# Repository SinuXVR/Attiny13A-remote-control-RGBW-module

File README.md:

# Attiny13A based remote control RGB module

# Features

* 3 independent software PWM channel to control RGB led
* Works with cheap 24-key IR remote controller (NEC protocol)
* 16 static colors and 4 special effects
* 5 brightness levels (for static colors) and variable special effects speed
* Power ON/OFF feature
* Power consumption in OFF mode is less than 0.8mA (depends on IR receiver)
* Supply voltage: 3V to 6V (single Li-ion, 3xLR06, USB)
* Size: 868 bytes

# Remote controller

||
|:---:|
||

### Showcase

|||||
|:---:|:---:|:---:|:---:|

#### Special effects

|**Flash**|**Smooth**|
|:-------:|:--------:|
|||
|**Strobe**|**Fade**|
|||

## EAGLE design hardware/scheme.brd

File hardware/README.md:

# Circuit and board

|||
|:---:|:---:|

Made in EAGLE 9.4.2

# Bill Of Materials

|**Item**|**Quantity**|**Description**|
|:------:|:----------:|:--------------|
|D*|10|5050 RGB LED|
|Q*|3|SOT-23 N-channel MOSFET with Imax > 100mA (AO3400, IRLML2502TR)|
|R1, R3|2|15 Ohms 1206 resistor|
|R2|1|27 Ohms 1206 resistor|
|R4|1|100 Ohms 0805 resistor|
|C1|1|10pF 0805 capacitor|
|C2|1|10uF 1206 capacitor|
|U2|1|IR receiver (VS1838B, TSOP4838 or similar)|
|IC1|1|ATTINY13-20SSU|

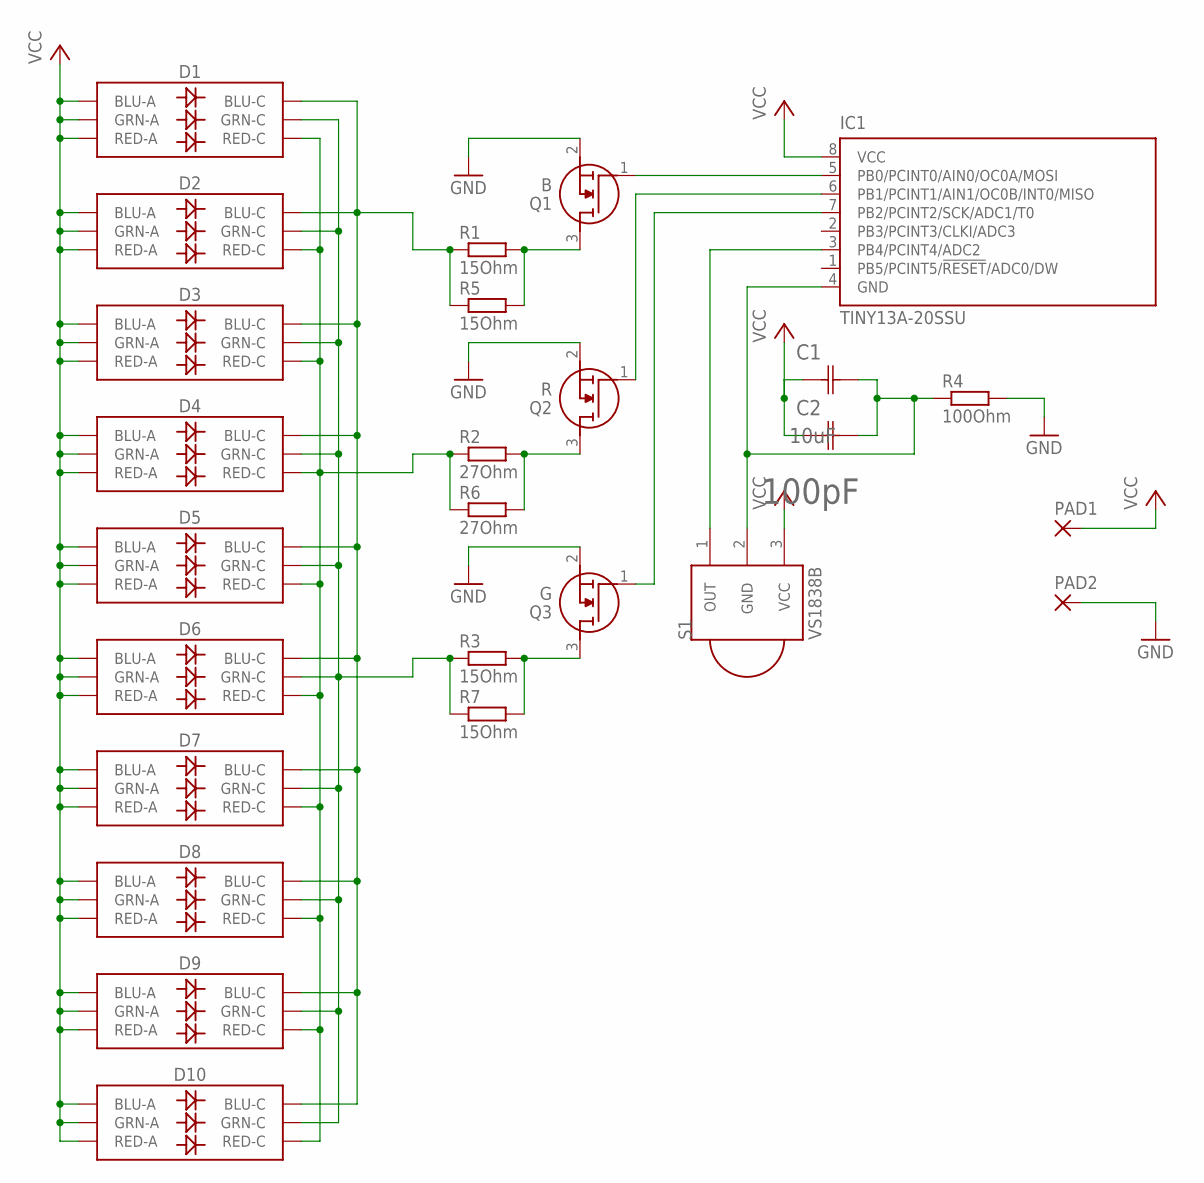
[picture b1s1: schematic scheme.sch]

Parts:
C1: 10uF; CAPC3216X94N
C2: 100pF; CAPC2013X94N
D1, D2, D3, D4, D5, D6, D7, D8, D9, D10: LED-RGBNO_IC; LED-TRICOLOR-5050
IC1: TINY13A-20SSU; 8S1
PAD1, PAD2: SMD2; SMD1,27-2,54
Q1: B; SOT95P280X125-3N
Q2: R; SOT95P280X125-3N
Q3: G; SOT95P280X125-3N
R1, R3: 15Ohm; R1206
R2: 27Ohm; R1206
R4: 100Ohm; R0805
R5, R7: 15Ohm; R0805
R6: 27Ohm; R0805
S1: VS1838B; PNA460XM

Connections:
GND: PAD2.1, Q1.2 (S), Q2.2 (S), Q3.2 (S), R4.2
unnamed: IC1.3 (PB4/PCINT4/ADC2), S1.1 (OUT)
unnamed: IC1.5 (PB0/PCINT0/AIN0/OC0A/MOSI), Q1.1 (G)
unnamed: IC1.6 (PB1/PCINT1/AIN1/OC0B/INT0/MISO), Q2.1 (G)
unnamed: IC1.7 (PB2/PCINT2/SCK/ADC1/T0), Q3.1 (G)
unnamed: D1.4 (GRN-C), D2.4 (GRN-C), D3.4 (GRN-C), D4.4 (GRN-C), D5.4 (GRN-C), D6.4 (GRN-C), D7.4 (GRN-C), D8.4 (GRN-C), D9.4 (GRN-C), D10.4 (GRN-C), R3.1, R7.1
unnamed: D1.6 (BLU-C), D2.6 (BLU-C), D3.6 (BLU-C), D4.6 (BLU-C), D5.6 (BLU-C), D6.6 (BLU-C), D7.6 (BLU-C), D8.6 (BLU-C), D9.6 (BLU-C), D10.6 (BLU-C), R1.1, R5.1
unnamed: Q1.3 (D), R1.2, R5.2
unnamed: Q2.3 (D), R2.2, R6.2
unnamed: Q3.3 (D), R3.2, R7.2
unnamed: C1.2 (C2), C2.2 (C2), IC1.4 (GND), R4.1, S1.2 (GND)
unnamed: D1.5 (RED-C), D2.5 (RED-C), D3.5 (RED-C), D4.5 (RED-C), D5.5 (RED-C), D6.5 (RED-C), D7.5 (RED-C), D8.5 (RED-C), D9.5 (RED-C), D10.5 (RED-C), R2.1, R6.1
VCC: C1.1 (C1), C2.1 (C1), D1.1 (BLU-A), D1.2 (RED-A), D1.3 (GRN-A), D2.1 (BLU-A), D2.2 (RED-A), D2.3 (GRN-A), D3.1 (BLU-A), D3.2 (RED-A), D3.3 (GRN-A), D4.1 (BLU-A), D4.2 (RED-A), D4.3 (GRN-A), D5.1 (BLU-A), D5.2 (RED-A), D5.3 (GRN-A), D6.1 (BLU-A), D6.2 (RED-A), D6.3 (GRN-A), D7.1 (BLU-A), D7.2 (RED-A), D7.3 (GRN-A), D8.1 (BLU-A), D8.2 (RED-A), D8.3 (GRN-A), D9.1 (BLU-A), D9.2 (RED-A), D9.3 (GRN-A), D10.1 (BLU-A), D10.2 (RED-A), D10.3 (GRN-A), IC1.8 (VCC), PAD1.1, S1.3 (VCC)

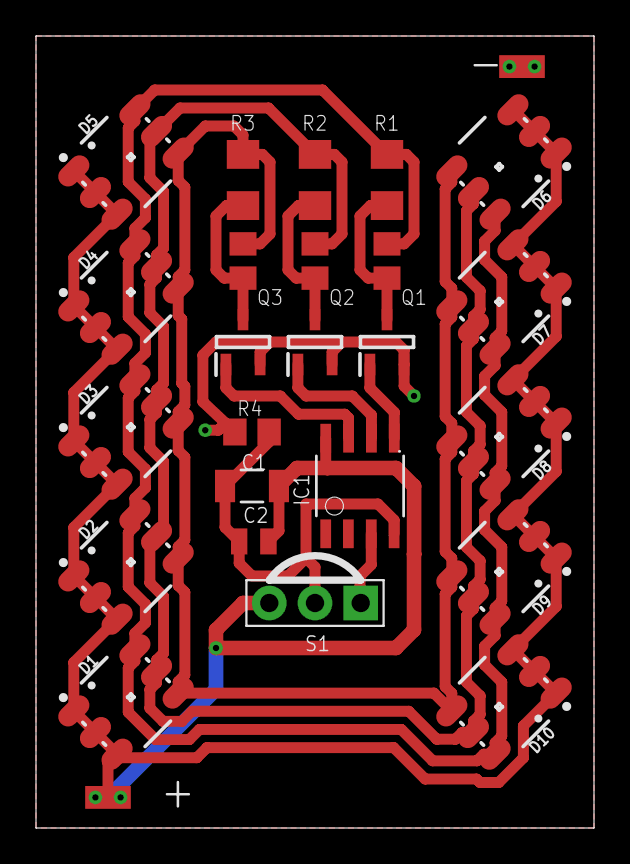
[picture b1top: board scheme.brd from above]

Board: 2 copper layers, 31.0 x 44.0 mm, 26 parts (0 on the bottom side), 13 nets.

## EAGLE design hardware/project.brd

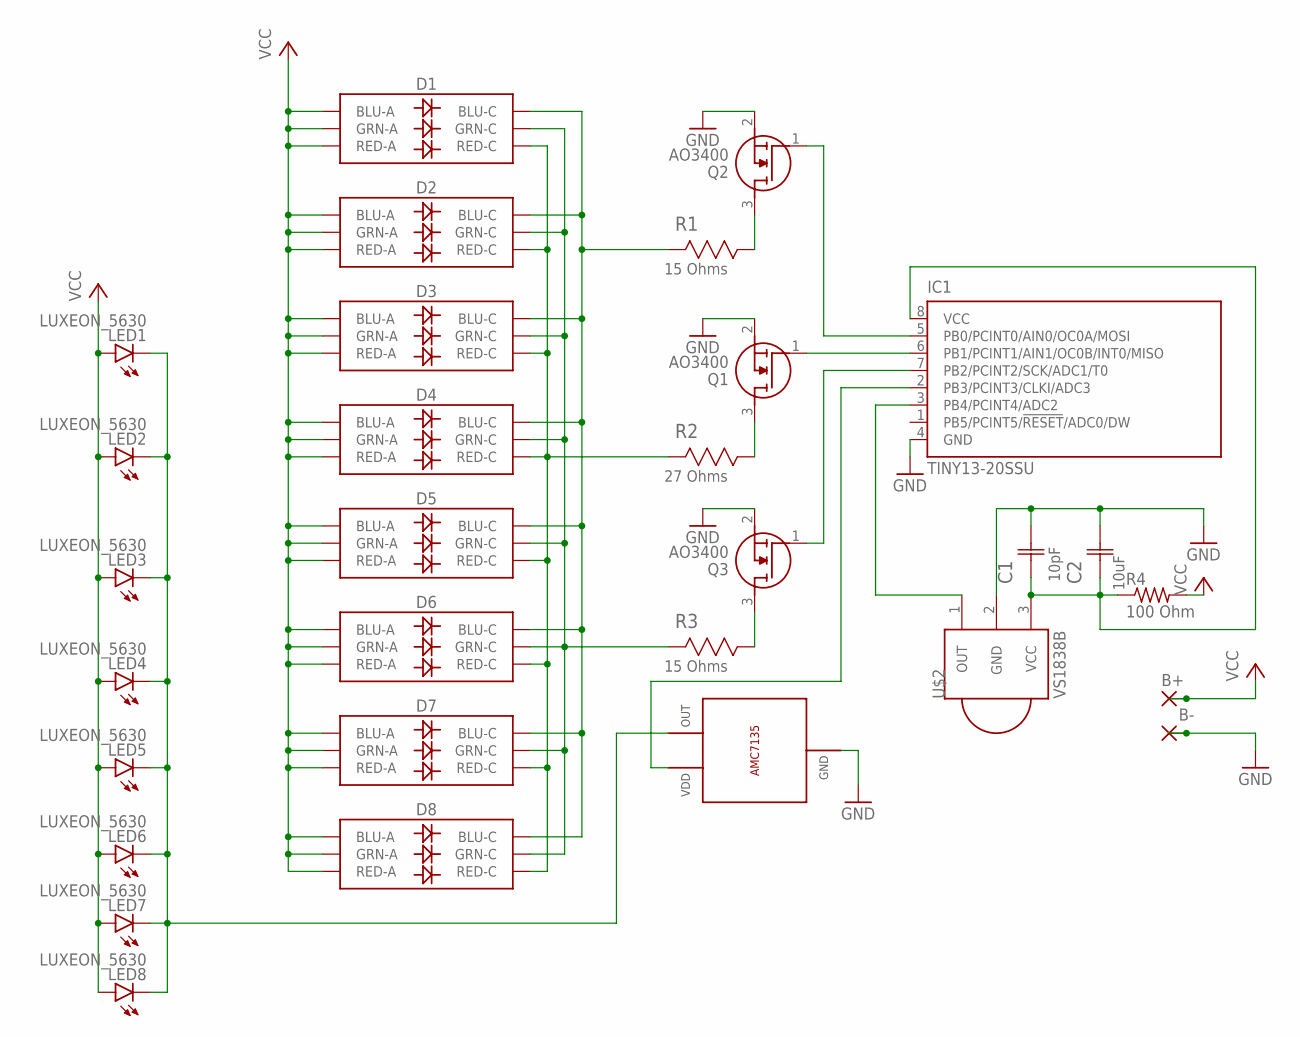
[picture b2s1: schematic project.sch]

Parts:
B+: WIREPADSMD1,27-254; SMD1,27-2,54
B-: WIREPADSMD1,27-254; SMD1,27-2,54
C1: 10pF; CAPC2013X94N
C2: 10uF; CAPC3216X94N
D1, D2, D3, D4, D5, D6, D7, D8: LED-RGBNO_IC; LED-TRICOLOR-5050
IC1: TINY13-20SSU; 8S1
LED1, LED2, LED3, LED4, LED5, LED6, LED7, LED8: LUXEON_5630
Q1, Q2, Q3: AO3400; SOT95P280X125-3N
R1, R3: 15 Ohms; RESC3216X71N
R2: 27 Ohms; RESC3216X71N
R4: 100 Ohm; R0805
U$1: AMC7135
U$2: VS1838B; PNA460XM

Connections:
GND: B-.1, C1.2 (C2), C2.2 (C2), IC1.4 (GND), Q1.2 (S), Q2.2 (S), Q3.2 (S), U$1.GND, U$1.TAB (GND), U$2.2 (GND)
unnamed: LED1.1@1 (C), LED1.1@2 (C), LED2.1@1 (C), LED2.1@2 (C), LED3.1@1 (C), LED3.1@2 (C), LED4.1@1 (C), LED4.1@2 (C), LED5.1@1 (C), LED5.1@2 (C), LED6.1@1 (C), LED6.1@2 (C), LED7.1@1 (C), LED7.1@2 (C), LED8.1@1 (C), LED8.1@2 (C), U$1.OUT
unnamed: IC1.5 (PB0/PCINT0/AIN0/OC0A/MOSI), Q2.1 (G)
unnamed: IC1.6 (PB1/PCINT1/AIN1/OC0B/INT0/MISO), Q1.1 (G)
unnamed: IC1.7 (PB2/PCINT2/SCK/ADC1/T0), Q3.1 (G)
unnamed: Q2.3 (D), R1.1 (R1)
unnamed: Q1.3 (D), R2.1 (R1)
unnamed: Q3.3 (D), R3.1 (R1)
unnamed: D1.5 (RED-C), D2.5 (RED-C), D3.5 (RED-C), D4.5 (RED-C), D5.5 (RED-C), D6.5 (RED-C), D7.5 (RED-C), D8.5 (RED-C), R2.2 (R2)
unnamed: D1.6 (GRN-C), D2.6 (GRN-C), D3.6 (GRN-C), D4.6 (GRN-C), D5.6 (GRN-C), D6.6 (GRN-C), D7.6 (GRN-C), D8.6 (GRN-C), R3.2 (R2)
unnamed: D1.4 (BLU-C), D2.4 (BLU-C), D3.4 (BLU-C), D4.4 (BLU-C), D5.4 (BLU-C), D6.4 (BLU-C), D7.4 (BLU-C), D8.4 (BLU-C), R1.2 (R2)
unnamed: IC1.3 (PB4/PCINT4/ADC2), U$2.1 (OUT)
unnamed: IC1.2 (PB3/PCINT3/CLKI/ADC3), U$1.VDD
unnamed: C1.1 (C1), C2.1 (C1), IC1.8 (VCC), R4.1, U$2.3 (VCC)
VCC: B+.1, D1.1 (GRN-A), D1.2 (RED-A), D1.3 (BLU-A), D2.1 (GRN-A), D2.2 (RED-A), D2.3 (BLU-A), D3.1 (GRN-A), D3.2 (RED-A), D3.3 (BLU-A), D4.1 (GRN-A), D4.2 (RED-A), D4.3 (BLU-A), D5.1 (GRN-A), D5.2 (RED-A), D5.3 (BLU-A), D6.1 (GRN-A), D6.2 (RED-A), D6.3 (BLU-A), D7.1 (GRN-A), D7.2 (RED-A), D7.3 (BLU-A), D8.1 (GRN-A), D8.2 (RED-A), D8.3 (BLU-A), LED1.2 (A), LED2.2 (A), LED3.2 (A), LED4.2 (A), LED5.2 (A), LED6.2 (A), LED7.2 (A), LED8.2 (A), R4.2

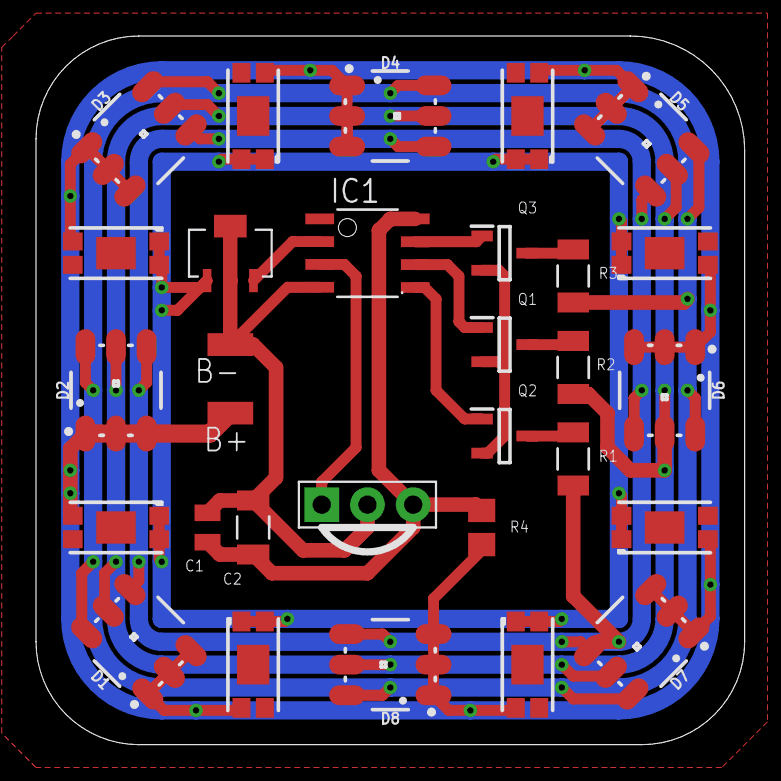
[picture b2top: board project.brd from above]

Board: 2 copper layers, 39.4 x 39.4 mm, 30 parts (0 on the bottom side), 15 nets.

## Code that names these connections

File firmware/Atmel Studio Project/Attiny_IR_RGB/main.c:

/**
 * Chip type: Attiny13
 * Clock frequency: 4.8MHz without divider
 * Flash command: avrdude -p t13 -c avrisp -b 19200 -u -Uflash:w:Attiny_IR_RGB.hex:a -Ulfuse:w:0x71:m -Uhfuse:w:0xFF:m
 *                       +--------+
 *        [        (PB5) |1*     8| (VCC)  Power ]
 *        [        (PB3) |2      7| (PB2)   BLUE ]
 *        [ VS1838 (PB4) |3      6| (PB1)  GREEN ]
 *        [ Ground (GND) |4      5| (PB0)    RED ]
 *                       +--------+
 */

#define F_CPU 4800000UL
#include <avr/io.h>
#include "lib/common.h"
#include "lib/ir.h"
#include "lib/led_pwm.h"
#include "lib/animation.h"

// Entry point
int main(void) {
	// Set up
	power_off_init();
	pwm_init_rgb();
	ir_init();
	
	// Initial state - STATE_COLOR with power off bit
	byte current_state = STATE_COLOR | 0x80;
	
	// Animation and brightness parameters
	byte anim_rate = ANIM_RATE_INITIAL_VALUE;
	byte anim_counter = 0;
	byte anim_local_counter = 0;
	byte brightness = BRIGHTNESS_INITIAL_VALUE;
	
	// Main loop
	while(1) {
		// Check if new command was received and change state
		if (ir_has_new_command()) {
			byte command = ir_get_received_command();

			// Power on and power off
			if (command == IR_KEY_POWER_ON) {
				clear_power_off_bit(current_state);
				continue;
			}
			if (command == IR_KEY_POWER_OFF) {
				set_power_off_bit(current_state);
				continue;
			}
			
			// Ignore other commands during sleep
			if (has_power_off_bit(current_state)) continue;
			
			// Change brightness or animation speed depending on current mode
			if (command == IR_KEY_UP) {
				if (current_state == STATE_COLOR) {
					brightness = anim_inc_brightness(brightness);
				}
				else {
					anim_rate = anim_dec_rate(anim_rate);
				}
				continue;
			}
			if (command == IR_KEY_DOWN) {
				if (current_state == STATE_COLOR) {
					brightness = anim_dec_brightness(brightness);
				}
				else {
					anim_rate = anim_inc_rate(anim_rate);
				}
				continue;
			}
			
			// Change animation modes
			if (command == IR_KEY_ANIM_RAINBOW) {
				current_state = STATE_RAINBOW_ANIMATION;
				continue;
			}
			if (command == IR_KEY_ANIM_JUMP) {
				current_state = STATE_JUMP_ANIMATION;
				continue;
			}
			if (command == IR_KEY_ANIM_FADE) {
				current_state = STATE_FADE_ANIMATION;
				continue;
			}
			if (command == IR_KEY_ANIM_STROBE) {
				current_state = STATE_STROBE_ANIMATION;
				// For some reason this continue increases code size
				// continue;
			}
			
			// Otherwise try to set color value
			if (anim_set_color_by_key(command)) {
				current_state = STATE_COLOR;
				anim_set_brightness(brightness);
			}
		}
		
		// If IR_KEY_POWER_OFF has been pressed - disable all outputs and go to sleep
		if (has_power_off_bit(current_state)) {
			if (ir_is_idle_state()) power_off();
			continue;
		}
		
		// Calculate animation step
		if (++anim_counter >= anim_rate) {
			if (current_state == STATE_JUMP_ANIMATION) anim_jump(anim_local_counter); else
			if (current_state == STATE_FADE_ANIMATION) anim_fade(anim_local_counter); else
			if (current_state == STATE_STROBE_ANIMATION) anim_strobe(anim_local_counter); else
			if (current_state == STATE_RAINBOW_ANIMATION) anim_rainbow();
			anim_local_counter++;
			anim_counter = 0;
		}
		
		// Do PWM
		pwm_rgb(r_current_value, g_current_value, b_current_value);

	}
	
	return 0;
}

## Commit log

2021-01-08 Link fix
2021-01-10 Cleanup
2022-01-11 RGB version

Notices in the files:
parts and their libraries:
SparkFun-LED: Licensing: Creative Commons ShareAlike 4.0 International - https://creativecommons.org/licenses/by-sa/4.0
led: Lumileds 5630 Datasheet DS201 20130228 ©2013 Philips Lumileds Lighting Company.
